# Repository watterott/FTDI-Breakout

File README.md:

# FTDI-Breakout
The FTDI-Breakout is an USB to Serial Adapter with FTDI Chipset.

* [FTDI FT231X](https://www.ftdichip.com/Products/ICs/FT231X.html) USB UART Bridge (up to 1M baud)
* 3.3V or 5V logic supply voltage selectable by switch
* Rx + Tx Status LEDs
* Overcurrent protection (resettable polyswitch fuse)
* Standard 6 pin connector with GND, CTS, VCC, TX, RX, DTR
* USB connector
* Open-Source and released under the [Creative Commons Attribution Share-Alike License](https://creativecommons.org/licenses/by-sa/4.0/).
* **[Documentation on learn.watterott.com](https://learn.watterott.com)**

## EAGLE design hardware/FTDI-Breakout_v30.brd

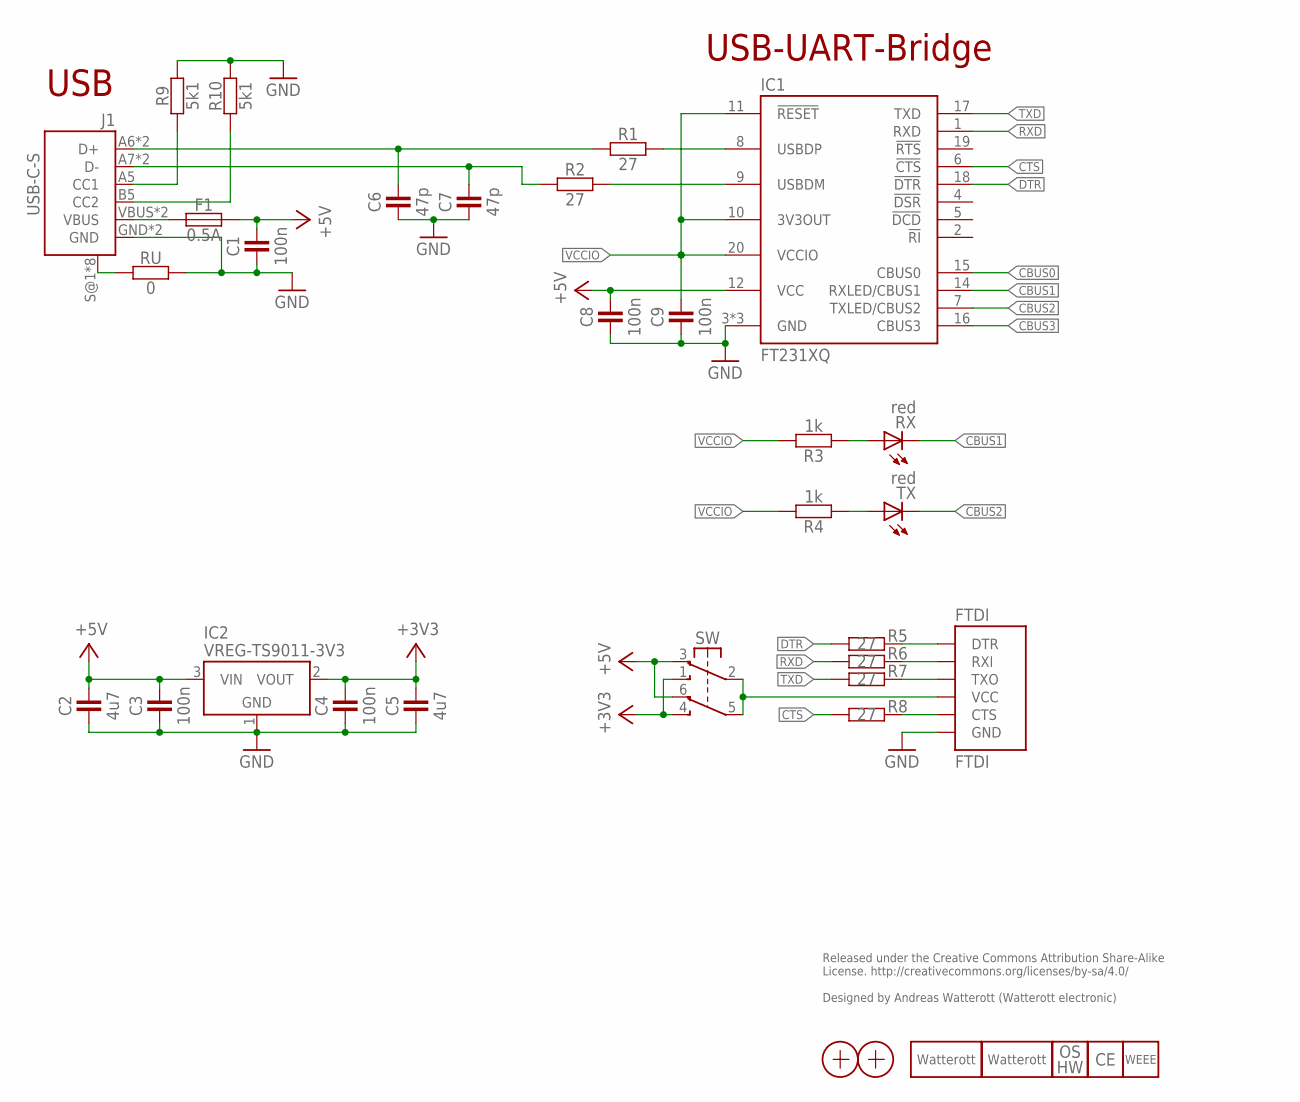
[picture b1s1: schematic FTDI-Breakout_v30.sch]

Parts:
C1, C3, C4, C8, C9: 100n; C0603
C2, C5: 4u7; C0805
C6, C7: 47p; C0603
F1: 0.5A; C0805
FTDI: FTDI
IC1: FT231XQ; QFN20-PAD
IC2: VREG-TS9011-3V3; SOT23
J1: USB-C-S
LOGO5: LOGO_SPARK-2; SPARK_2MM
LOGO6: LOGO_SPARK-4; SPARK_4MM
LOGO7: LOGO_OSHW-2; OSHW_2MM
LOGO8: LOGO_CE-2; CE_2MM
LOGO9: LOGO_WEEE-4; WEEE_4MM
R1, R2, R5, R6, R7, R8: 27; C0603
R3, R4: 1k; C0603
R9, R10: 5k1; C0603
RU: 0; C0603
RX: red; C0603
SW: SW-2UM-CUS22B; CUS22B
TX: red; C0603
X1, X2: PASSER-07; PASSER_07MM

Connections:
+3V3: C4.2, C5.2, IC2.2 (VOUT), SW.1 (NO1), SW.4 (NO2)
+5V: C1.2, C2.2, C3.2, C8.2, F1.2, IC1.12 (VCC), IC2.3 (VIN), SW.3 (NC1), SW.6 (NC2)
CBUS0: IC1.15 (CBUS0)
CBUS1: IC1.14 (RXLED/CBUS1), RX.C
CBUS2: IC1.7 (TXLED/CBUS2), TX.C
CBUS3: IC1.16 (CBUS3)
CC1: J1.A5 (CC1), R9.1
CC2: J1.B5 (CC2), R10.1
CTS: IC1.6 (!CTS), R8.1
D2_N: IC1.9 (USBDM), R2.2
D2_P: IC1.8 (USBDP), R1.2
DTR: IC1.18 (!DTR), R5.1
D_N: C7.2, J1.A7 (D-), J1.B7 (D-), R2.1
D_P: C6.2, J1.A6 (D+), J1.B6 (D+), R1.1
FTDI-CTS: FTDI.2-CTS (CTS), R8.2
FTDI-DTR: FTDI.6-DTR (DTR), R5.2
FTDI-RXI: FTDI.5-RXI (RXI), R6.2
FTDI-TXO: FTDI.4-TXO (TXO), R7.2
FTDI-VCC: FTDI.3-VCC (VCC), SW.2 (C1), SW.5 (C2)
GND: C1.1, C2.1, C3.1, C4.1, C5.1, C6.1, C7.1, C8.1, C9.1, FTDI.1-GND (GND), IC1.3 (GND), IC1.13 (GND), IC1.TP (GND), IC2.1 (GND), J1.GND, J1.GND2 (GND), R9.2, R10.2, RU.2
RX-LED: R3.1, RX.A
RXD: IC1.1 (RXD), R6.1
SHLD: J1.S@1 (SHIELD), J1.S@2 (SHIELD), J1.S@3 (SHIELD), J1.S@4 (SHIELD), J1.S@5 (SHIELD), J1.S@6 (SHIELD), J1.S@7 (SHIELD), J1.S@8 (SHIELD), RU.1
TX-LED: R4.1, TX.A
TXD: IC1.17 (TXD), R7.1
VBUS: F1.1, J1.VBUS, J1.VBUS2 (VBUS)
VCCIO: C9.2, IC1.10 (3V3OUT), IC1.11 (!RESET), IC1.20 (VCCIO), R3.2, R4.2

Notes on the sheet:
Released under the Creative Commons Attribution Share-Alike License. http://creativecommons.org/licenses/by-sa/4.0/ Designed by Andreas Watterott (Watterott electronic)
USB-UART-Bridge
USB

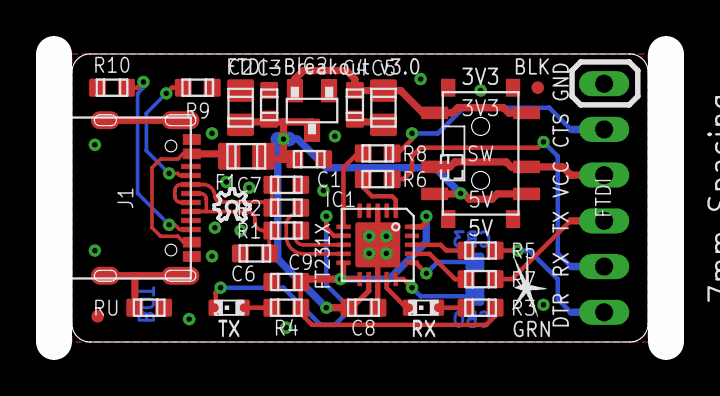
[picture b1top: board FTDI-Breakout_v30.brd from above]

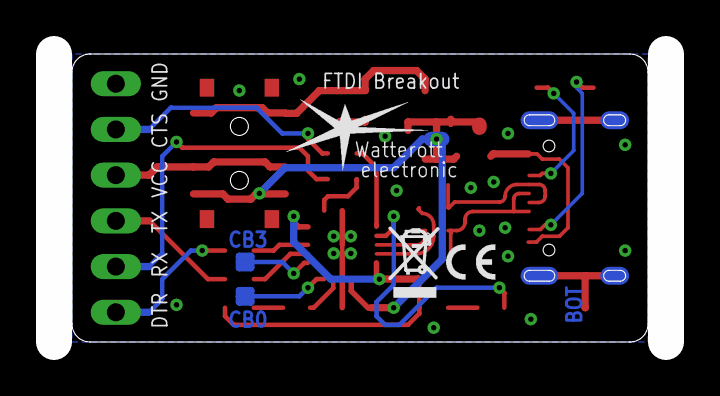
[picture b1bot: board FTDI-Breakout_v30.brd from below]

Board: 2 copper layers, 34.0 x 16.0 mm, 35 parts (3 on the bottom side), 25 nets.

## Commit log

2018-07-30 added rev 2.1
2018-10-27 updated schematics
2020-07-28 added rev 3.0 (USB-C)
2020-08-12 added v3 photo
